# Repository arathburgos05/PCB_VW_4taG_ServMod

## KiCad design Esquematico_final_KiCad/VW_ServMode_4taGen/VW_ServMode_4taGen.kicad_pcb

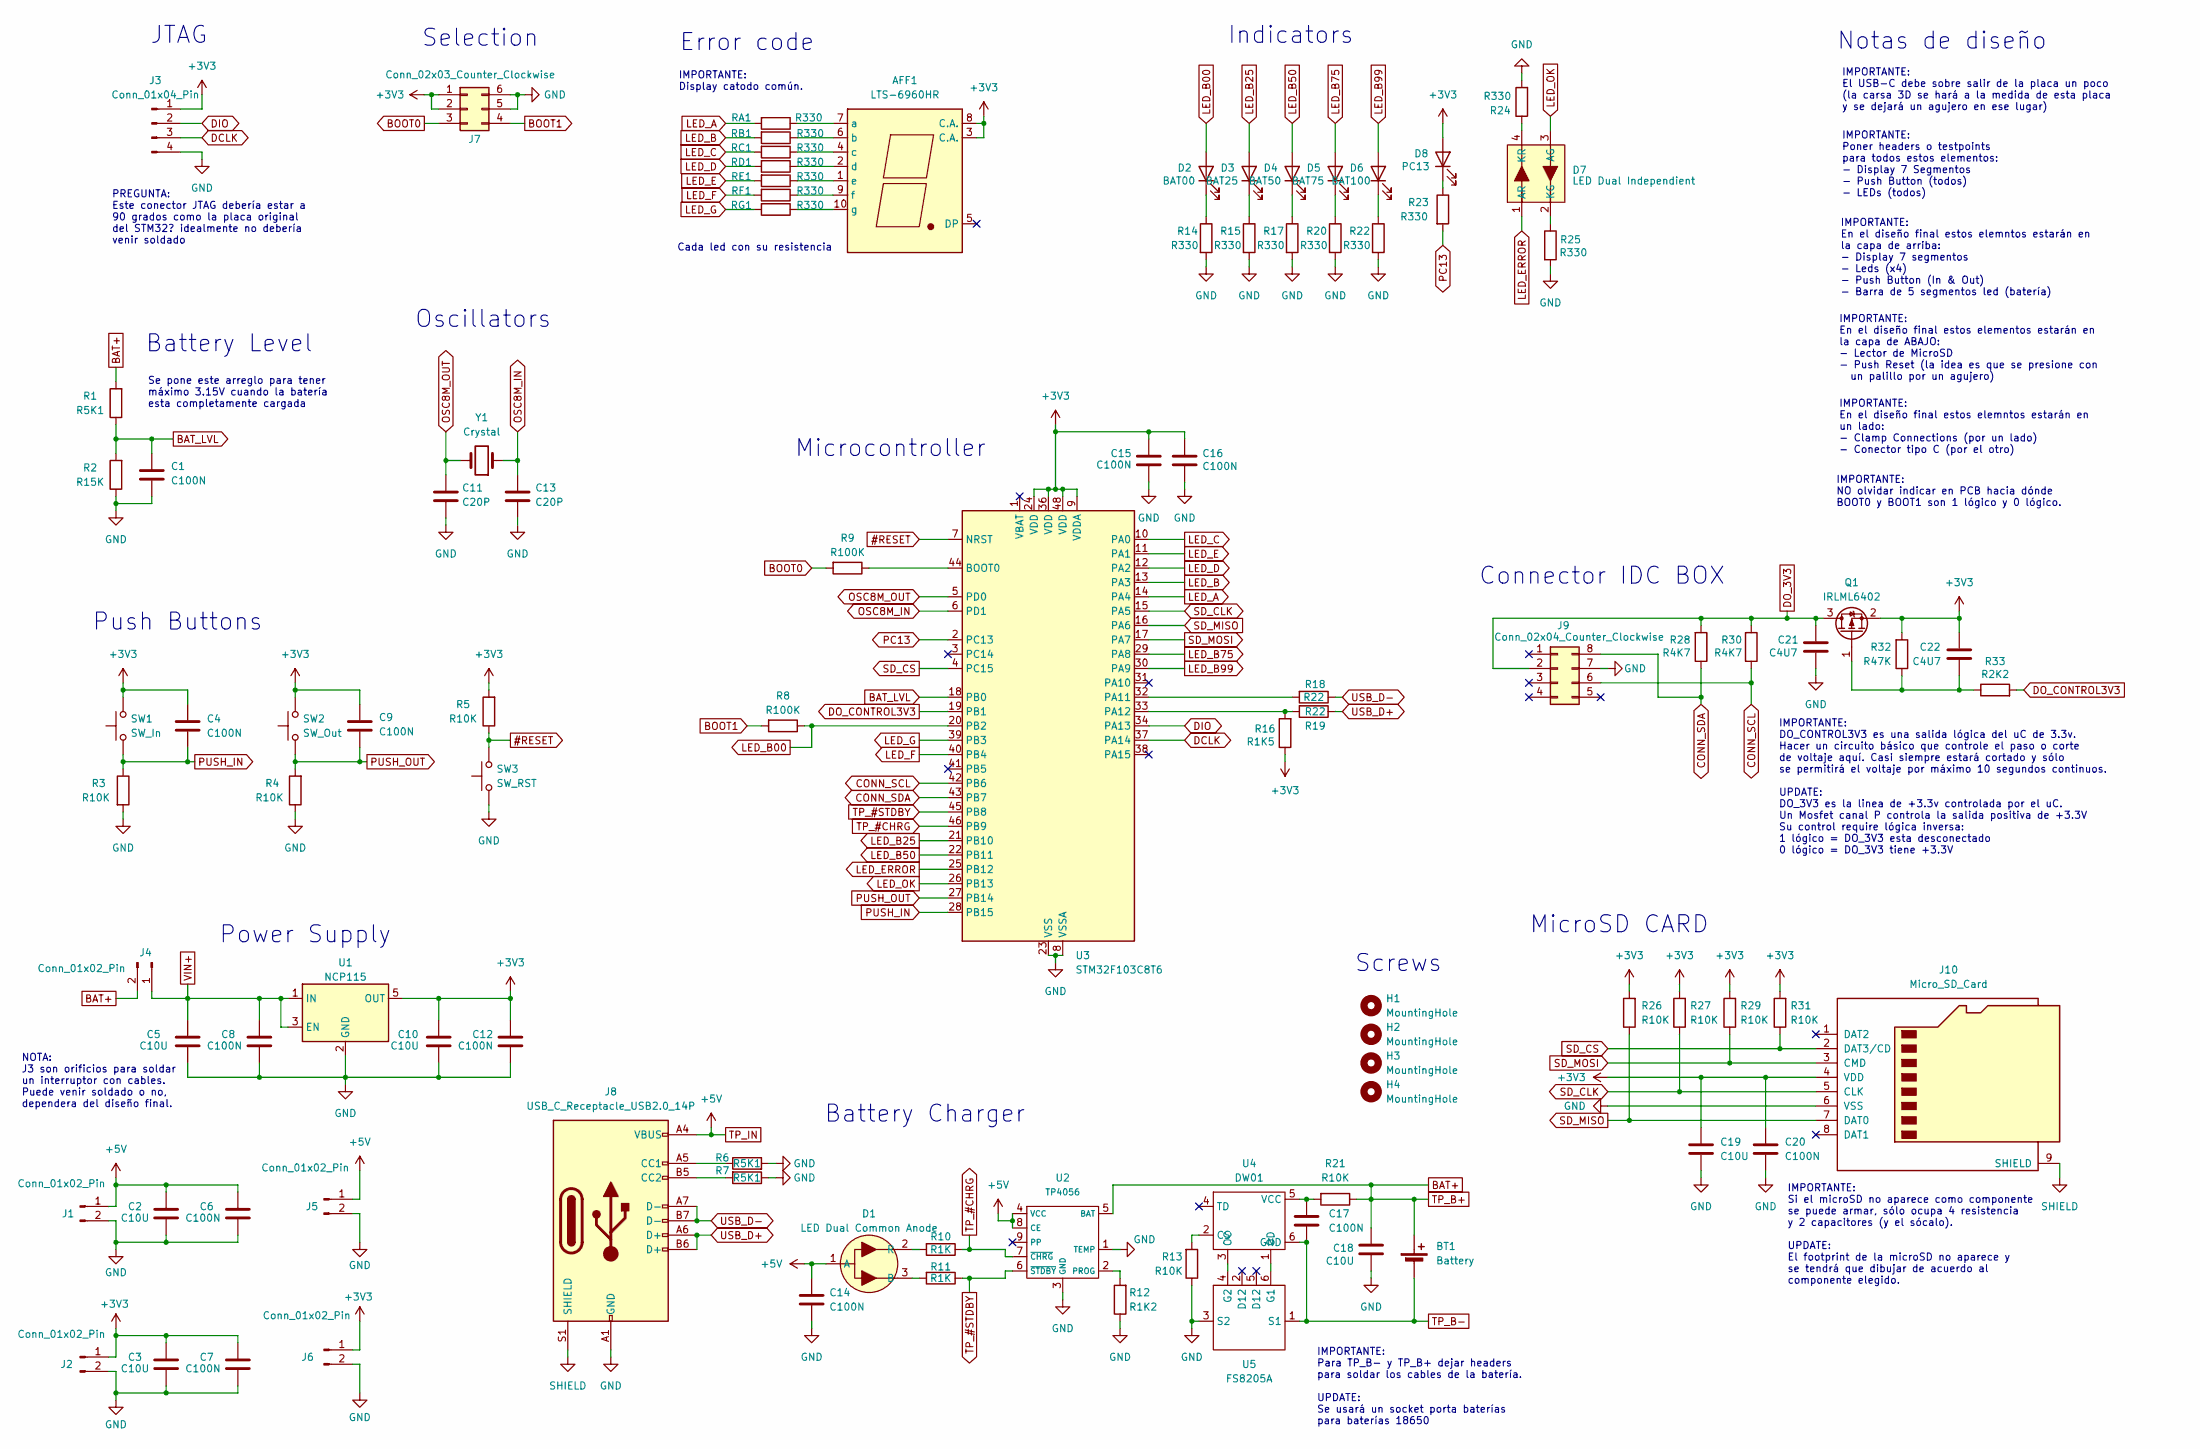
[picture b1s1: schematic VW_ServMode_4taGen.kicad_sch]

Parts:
AFF1: LTS-6960HR; 7SegmentLED_LTS6760_LTS6780; JLCPCB Part # C8092
BT1: Battery; BatteryHolder_Keystone_1042_1x18650; JLCPCB Part # C2988620
C1, C4, C6, C7, C8, C9, C12, C14, C15, C16, C17, C20: C100N; C_0603_1608Metric
C2, C3, C5, C10, C18, C19: C10U; C_0603_1608Metric
C11, C13: C20P; C_0603_1608Metric
C21, C22: C4U7; C_0603_1608Metric
D1: LED Dual Common Anode; SMD,2x3mm
D2: BAT00; LED_Rectangular_W5.0mm_H2.0mm
D3: BAT25; LED_Rectangular_W5.0mm_H2.0mm
D4: BAT50; LED_Rectangular_W5.0mm_H2.0mm
D5: BAT75; LED_Rectangular_W5.0mm_H2.0mm
D6: BAT100; LED_Rectangular_W5.0mm_H2.0mm
D7: LED Dual Independient; SMD-4P,3.5x2.8mm
D8: PC13; LED_0805_2012Metric
H1, H2, H3, H4: MountingHole; MountingHole_3.2mm_M3
J1, J2, J4, J5, J6: Conn_01x02_Pin; PinHeader_1x02_P2.54mm_Vertical
J3: Conn_01x04_Pin; PinHeader_1x04_P2.54mm_Vertical
J7: Conn_02x03_Counter_Clockwise; PinHeader_2x03_P2.54mm_Vertical
J8: USB_C_Receptacle_USB2.0_14P; USB_C_Receptacle_G-Switch_GT-USB-7010ASV
J9: Conn_02x04_Counter_Clockwise; IDC-Header_2x04_P2.54mm_Horizontal
J10: Micro_SD_Card; MicroSD_Memory
Q1: IRLML6402; SOT-23
R1, R6, R7: R5K1; R_0603_1608Metric
R2: R15K; R_0603_1608Metric
R3, R4, R5, R13, R21, R26, R27, R29, R31: R10K; R_0603_1608Metric
R8, R9: R100K; R_0603_1608Metric
R10, R11: R1K; R_0603_1608Metric
R12: R1K2; R_0603_1608Metric
R14, R15, R17, R20, R22, R23, R24, R25: R330; R_0603_1608Metric
R16: R1K5; R_0603_1608Metric
R18, R19: R22; R_0603_1608Metric
R28, R30: R4K7; R_0603_1608Metric
R32: R47K; R_0603_1608Metric
R33: R2K2; R_0603_1608Metric
RA1: R330; R_0603_1608Metric
RB1: R330; R_0603_1608Metric
RC1: R330; R_0603_1608Metric
RD1: R330; R_0603_1608Metric
RE1: R330; R_0603_1608Metric
RF1: R330; R_0603_1608Metric
RG1: R330; R_0603_1608Metric
SW1: SW_In; SW_SPST_Omron_B3FS-105xP
SW2: SW_Out; SW_SPST_Omron_B3FS-105xP
SW3: SW_RST; SW_SPST_Omron_B3FS-105xP
U1: NCP115; TSOP-5_1.65x3.05mm_P0.95mm
U2: TP4056; SOIC-8-1EP_3.9x4.9mm_P1.27mm_EP2.29x3mm
U3: STM32F103C8T6; LQFP-48_7x7mm_P0.5mm
U4: DW01; SOT-23-6_Handsoldering
U5: FS8205A; SOT-23-6_Handsoldering
Y1: Crystal; Crystal_SMD_ECS_CSM3X-2Pin_7.6x4.1mm

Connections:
#RESET: R5.1, SW3.2, U3.7 (NRST)
BAT+: BT1.1 (+), C18.2, J4.2, R1.2, R21.1, U2.5 (BAT)
BAT_LVL: C1.2, R1.1, R2.2, U3.18 (PB0)
BOOT0: J7.3, R9.2
BOOT1: J7.4, R8.2
CONN_SCL: J9.6, R30.1, U3.42 (PB6)
CONN_SDA: J9.8, R28.1, U3.43 (PB7)
DCLK: J3.3, U3.37 (PA14)
DIO: J3.2, U3.34 (PA13)
DO_3V3: C21.2, J9.2, Q1.3 (D), R28.2, R30.2
DO_CONTROL3V3: R33.2, U3.19 (PB1)
LED_A: RA1.2, U3.14 (PA4)
LED_B: RB1.2, U3.13 (PA3)
LED_B00: D2.2 (A), R8.1, U3.20 (PB2)
LED_B25: D3.2 (A), U3.21 (PB10)
LED_B50: D4.2 (A), U3.22 (PB11)
LED_B75: D5.2 (A), U3.29 (PA8)
LED_B99: D6.2 (A), U3.30 (PA9)
LED_C: RC1.2, U3.10 (PA0)
LED_D: RD1.2, U3.12 (PA2)
LED_E: RE1.2, U3.11 (PA1)
LED_ERROR: D7.1 (AR), U3.25 (PB12)
LED_F: RF1.2, U3.40 (PB4)
LED_G: RG1.2, U3.39 (PB3)
LED_OK: D7.3 (AG), U3.26 (PB13)
unnamed: AFF1.7 (a), RA1.1
unnamed: AFF1.6 (b), RB1.1
unnamed: AFF1.4 (c), RC1.1
unnamed: AFF1.2 (d), RD1.1
unnamed: AFF1.1 (e), RE1.1
unnamed: AFF1.9 (f), RF1.1
unnamed: AFF1.10 (g), RG1.1
unnamed: D1.3 (B), R11.2
unnamed: D1.2 (R), R10.2
unnamed: D2.1 (K), R14.1
unnamed: D3.1 (K), R15.1
unnamed: D4.1 (K), R17.1
unnamed: D5.1 (K), R20.1
unnamed: D6.1 (K), R22.1
unnamed: D7.2 (KG), R25.1
unnamed: D7.4 (KR), R24.1
unnamed: D8.1 (K), R23.1
unnamed: J8.A5 (CC1), R6.1
unnamed: J8.B5 (CC2), R7.2
unnamed: C22.1, Q1.1 (G), R32.1, R33.1
unnamed: R12.2, U2.2 (PROG)
unnamed: R9.1, U3.44 (BOOT0)
unnamed: R18.2, U3.32 (PA11)
unnamed: R16.2, R19.2, U3.33 (PA12)
unnamed: R13.2, U4.2 (CS)
unnamed: U4.3 (OC), U5.4 (G2)
unnamed: U4.1 (OD), U5.6 (G1)
unnamed: C17.2, R21.2, U4.5 (VCC)
OSC8M_IN: C13.2, U3.6 (PD1), Y1.1
OSC8M_OUT: C11.2, U3.5 (PD0), Y1.2
PC13: R23.2, U3.2 (PC13)
PUSH_IN: C4.1, R3.1, SW1.1, U3.28 (PB15)
PUSH_OUT: C9.1, R4.2, SW2.1, U3.27 (PB14)
SD_CLK: J10.5 (CLK), R27.1, U3.15 (PA5)
SD_CS: J10.2 (DAT3/CD), R31.1, U3.4 (PC15)
SD_MISO: J10.7 (DAT0), R26.1, U3.16 (PA6)
SD_MOSI: J10.3 (CMD), R29.1, U3.17 (PA7)
SHIELD: J8.S1 (SHIELD), J10.9 (SHIELD)
TP_#CHRG: R10.1, U2.7 (~CHRG), U3.46 (PB9)
TP_#STDBY: R11.1, U2.6 (~STDBY), U3.45 (PB8)
TP_B-: BT1.2 (-), C17.1, U4.6 (GND), U5.1 (S1)
TP_IN: C2.2, C6.2, C14.2, D1.1 (A), J1.1, J5.1, J8.A4 (VBUS), J8.A9 (VBUS), J8.B4 (VBUS), J8.B9 (VBUS), U2.4 (VCC), U2.8 (CE)
USB_D+: J8.A6 (D+), J8.B6 (D+), R19.1
USB_D-: J8.A7 (D-), J8.B7 (D-), R18.1
VIN+: C5.2, C8.2, J4.1, U1.1 (IN), U1.3 (EN)

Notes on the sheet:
Power Supply
IMPORTANTE: Display catodo común.
Battery Charger
IMPORTANTE: Si el microSD no aparece como componente se puede armar, sólo ocupa 4 resistencia y 2 capacitores (y el sócalo). UPDATE: El footprint de la microSD no aparece y se tendrá que dibujar de acuerdo al componente elegido.
IMPORTANTE: DO_CONTROL3V3 es una salida lógica del uC de 3.3v. Hacer un circuito básico que controle el paso o corte de voltaje aquí. Casi siempre estará cortado y sólo se permitirá el voltaje por máximo 10 segundos continuos. UPDATE: DO_3V3 es la linea de +3.3v controlada por el uC. Un Mosfet cana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
NOTA: J3 son orificios para soldar un interruptor con cables. Puede venir soldado o no, dependera del diseño final.
IMPORTANTE: NO olvidar indicar en PCB hacia dónde BOOT0 y BOOT1 son 1 lógico y 0 lógico.
Push Buttons
IMPORTANTE: El USB-C debe sobre salir de la placa un poco (la carsa 3D se hará a la medida de esta placa y se dejará un agujero en ese lugar)
IMPORTANTE: Para TP_B- y TP_B+ dejar headers para soldar los cables de la batería. UPDATE: Se usará un socket porta baterías para baterías 18650
Oscillators
Selection
Battery Level
IMPORTANTE: Poner headers o testpoints para todos estos elementos: - Display 7 Segmentos - Push Button (todos) - LEDs (todos)
JTAG
IMPORTANTE: En el diseño final estos elementos estarán en la capa de ABAJO: - Lector de MicroSD - Push Reset (la idea es que se presione con un palillo por un agujero)
Microcontroller
Se pone este arreglo para tener máximo 3.15V cuando la batería esta completamente cargada
Error code
Screws
IMPORTANTE: En el diseño final estos elemntos estarán en la capa de arriba: - Display 7 segmentos - Leds (x4) - Push Button (In & Out) - Barra de 5 segmentos led (batería)
Indicators
PREGUNTA: Este conector JTAG debería estar a 90 grados como la placa original del STM32? idealmente no debería venir soldado
Cada led con su resistencia
Connector IDC BOX
Notas de diseño
IMPORTANTE: En el diseño final estos elemntos estarán en un lado: - Clamp Connections (por un lado) - Conector tipo C (por el otro)
MicroSD CARD

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
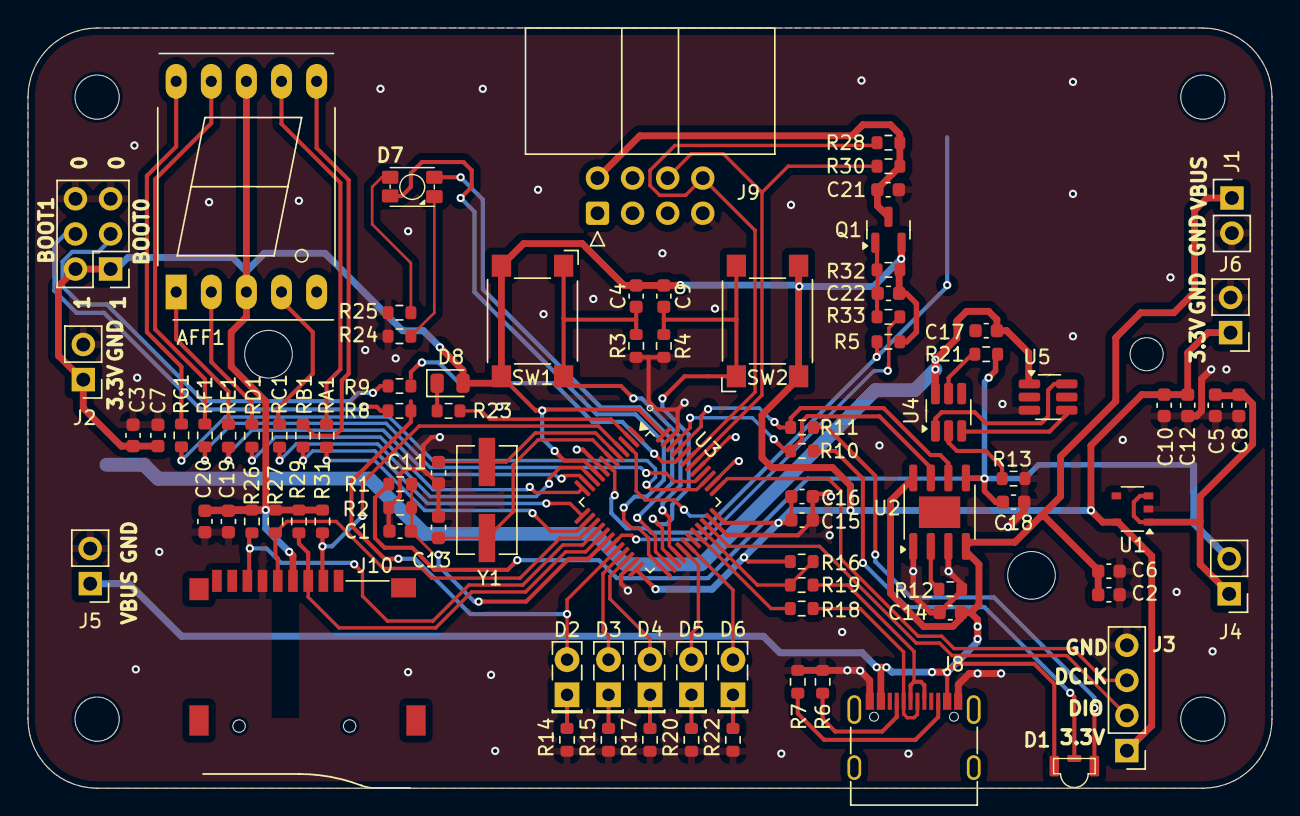
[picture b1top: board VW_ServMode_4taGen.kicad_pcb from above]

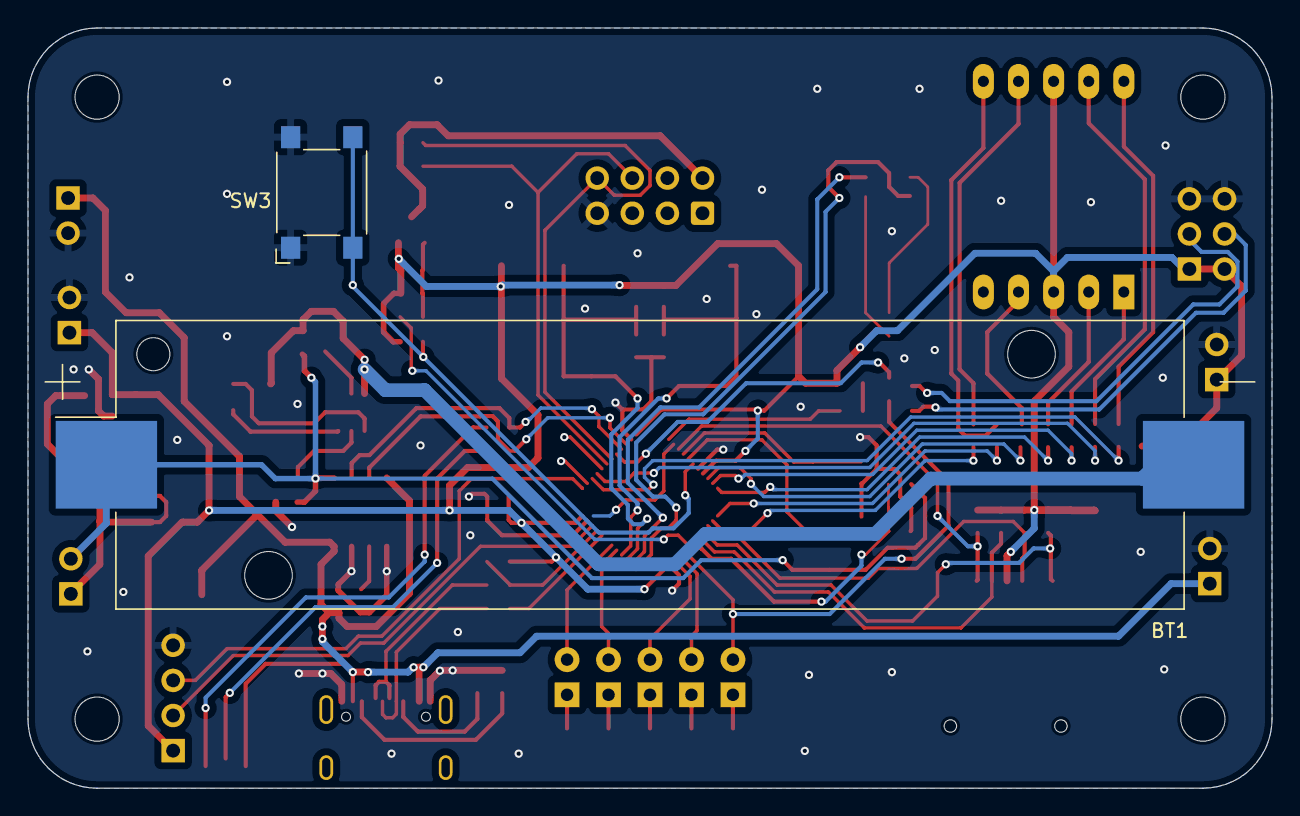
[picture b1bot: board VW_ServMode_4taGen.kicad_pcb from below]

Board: 2 copper layers, 90.0 x 55.0 mm, 97 parts (2 on the bottom side), 72 nets.

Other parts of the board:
H4#2: MountingHole; MountingHole_3.2mm_M3

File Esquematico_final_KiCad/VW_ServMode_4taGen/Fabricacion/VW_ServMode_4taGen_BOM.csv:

Comment,Designator,Footprint,Qty,JLCPCB Part #,Mouser Part #
LTS-6960HR,AFF1,Display_7Segment:7SegmentLED_LTS6760_LTS6780,1,C8092,604-SA05-11SURKWA
Battery,BT1,Battery:BatteryHolder_Keystone_1042_1x18650,1,-,-
C100N,"C1,C4,C6,C7,C8,C9,C12,C14,C15,C16,C17,C20",Capacitor_SMD:C_0603_1608Metric,12,C88136,80-C0603C101K5GAC
C10U,"C2,C3,C5,C10,C18,C19",Capacitor_SMD:C_0603_1608Metric,6,C91150,187-CL10A106MP8NNNC
C20P,"C11,C13",Capacitor_SMD:C_0603_1608Metric,2,C3008313,80-C0603C200J1HAUTO
C4U7,"C21,C22",Capacitor_SMD:C_0603_1608Metric,2,C69182,80-C0603C475M9PAC
LED Dual Common Anode,D1,"JCU_LED_SMD:SMD,2x3mm",1,C605447,859-LTST-S326TBKFKT
BAT00,D2,LED_THT:LED_Rectangular_W5.0mm_H2.0mm,1,C916069,604-WP113IDT
BAT25,D3,LED_THT:LED_Rectangular_W5.0mm_H2.0mm,1,C916069,604-WP113IDT
BAT50,D4,LED_THT:LED_Rectangular_W5.0mm_H2.0mm,1,C916069,604-WP113IDT
BAT75,D5,LED_THT:LED_Rectangular_W5.0mm_H2.0mm,1,C916069,604-WP113IDT
BAT100,D6,LED_THT:LED_Rectangular_W5.0mm_H2.0mm,1,C916069,604-WP113IDT
LED Dual Independient,D7,"JCU_LED_SMD:SMD-4P,3.5x2.8mm",1,C5355456,859-LTST-E682KRKGWT
PC13,D8,LED_SMD:LED_0805_2012Metric,1,C19273154,749-SM0805UBWC
Conn_01x02_Pin,"J1,J2,J4,J5,J6",Connector_PinHeader_2.54mm:PinHeader_1x02_P2.54mm_Vertical,5,-,-
Conn_01x04_Pin,J3,Connector_PinHeader_2.54mm:PinHeader_1x04_P2.54mm_Vertical,1,-,-
Conn_02x03_Counter_Clockwise,J7,Connector_PinHeader_2.54mm:PinHeader_2x03_P2.54mm_Vertical,1,C32713277,737-PH2-06-UA
USB_C_Receptacle_USB2.0_14P,J8,Connector_USB:USB_C_Receptacle_G-Switch_GT-USB-7010ASV,1,C2927038,640-USB4215-03-A
Conn_02x04_Counter_Clockwise,J9,Connector_IDC:IDC-Header_2x04_P2.54mm_Horizontal,1,C9139,523-G800W304018EU
Micro_SD_Card,J10,Own-Footprints:MicroSD_Memory,1,C29780377,-
IRLML6402,Q1,Package_TO_SOT_SMD:SOT-23,1,C2593,942-IRLML6402TRPBF
R5K1,"R1,R6,R7",Resistor_SMD:R_0603_1608Metric,3,C23186,603-RC0603JR-075K1L
R15K,R2,Resistor_SMD:R_0603_1608Metric,1,C22809,791-RMC1/16K1502FTP
R10K,"R3,R4,R5,R13,R21,R26,R27,R29,R31",Resistor_SMD:R_0603_1608Metric,9,C25804,603-RT0603FRD0710KL
R100K,"R8,R9",Resistor_SMD:R_0603_1608Metric,2,C25803,667-ERA-3AED104V
R1K,"R10,R11",Resistor_SMD:R_0603_1608Metric,2,C21190,71-CRCW06031K00FKECC
R1K2,R12,Resistor_SMD:R_0603_1608Metric,1,C22765,660-RN73H1JTD1201B50
R330,"R14,R15,R17,R20,R22,R23,R24,R25,RA1,RB1,RC1,RD1,RE1,RF1,RG1",Resistor_SMD:R_0603_1608Metric,15,C23138,603-RT0603FRE13330RL
R1K5,R16,Resistor_SMD:R_0603_1608Metric,1,C22843,603-RT0603FRE071K5L
R22,"R18,R19",Resistor_SMD:R_0603_1608Metric,2,C23345,603-RC0603JR-1322RL
R4K7,"R28,R30",Resistor_SMD:R_0603_1608Metric,2,C23162,667-ERA-3AEB472V
R47K,R32,Resistor_SMD:R_0603_1608Metric,1,C25819,603-RC0603JR-1047KL
R2K2,R33,Resistor_SMD:R_0603_1608Metric,1,C4190,603-RC0603JR-072K2L
SW_In,SW1,Button_Switch_SMD:SW_SPST_Omron_B3FS-105xP,1,C2888584,693-1301.9318
SW_Out,SW2,Button_Switch_SMD:SW_SPST_Omron_B3FS-105xP,1,C2888584,693-1301.9318
SW_RST,SW3,Button_Switch_SMD:SW_SPST_Omron_B3FS-105xP,1,C2888592,612-TL3301DF260QG
NCP115,U1,Package_SO:TSOP-5_1.65x3.05mm_P0.95mm,1,C603505,863-NCP115ASN330T2G
TP4056,U2,Package_SO:SOIC-8-1EP_3.9x4.9mm_P1.27mm_EP2.29x3mm,1,C382139,-
STM32F103C8T6,U3,Package_QFP:LQFP-48_7x7mm_P0.5mm,1,C8734,511-STM32F103C8T6TR
DW01,U4,Package_TO_SOT_SMD:SOT-23-6_Handsoldering,1,C86873,-
FS8205A,U5,Package_TO_SOT_SMD:SOT-23-6_Handsoldering,1,C908265,-
Crystal,Y1,Crystal:Crystal_SMD_ECS_CSM3X-2Pin_7.6x4.1mm,1,C5289691,-

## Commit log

2025-02-17 - Esquematico actualizado - PCB enrutado
2025-02-19 - BOM actualizado - Gerbers generados
2025-03-27 Errores corregidos - Resistencias en bus usb, leds cerca de usb, leds de nivel de batería
2025-04-06 Segunda version finalizada
